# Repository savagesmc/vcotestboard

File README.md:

# MAX2607 (Voltage Controlled Oscillator) Test Board.

this is an open source schemaatic and board layout for the [MAX2607 VCO](https://www.analog.com/en/products/max2607.html).

Analog Devices is selling their eval boards for over $200 USD, and the part itself is
just a couple of bucks. I'm just getting started desiging my own hardware,
so I figured I might as well practice my board design skills. I simply copied
The [eval board design taken from the Analog Devices website](
https://www.analog.com/media/en/technical-documentation/data-sheets/MAX2605EVKIT-MAX2609EVKIT.pdf).
I included placeholders for all of the resistors and inductors called out in that design,
so this board should work for testing all versions of the chip from the MAX2605
to the MAX2609.

I ordered 5 of these from [JLCPCB](https://jlcpcb.com). It was a very simple
process. I simply took the contents of the [gerbers folder](./gerbers), zipped
them up and uploaded the zipfile, and for $40 USD (including shipping), and about
2 weeks, I have a set of boards.

The version of the boards I ordered was commit 27e65ae6c2ac64e3f9bb4, which I later
noticed had a few things missing from the silkscreen, and I forgot to do the
mounting holes. I fixed those things, and that is the main HEAD commit.

So for about $12 USD total per board (board and parts), I now have 5 of these test boards.

If these devices pan out, I may use them in some future designs I am thinking through.

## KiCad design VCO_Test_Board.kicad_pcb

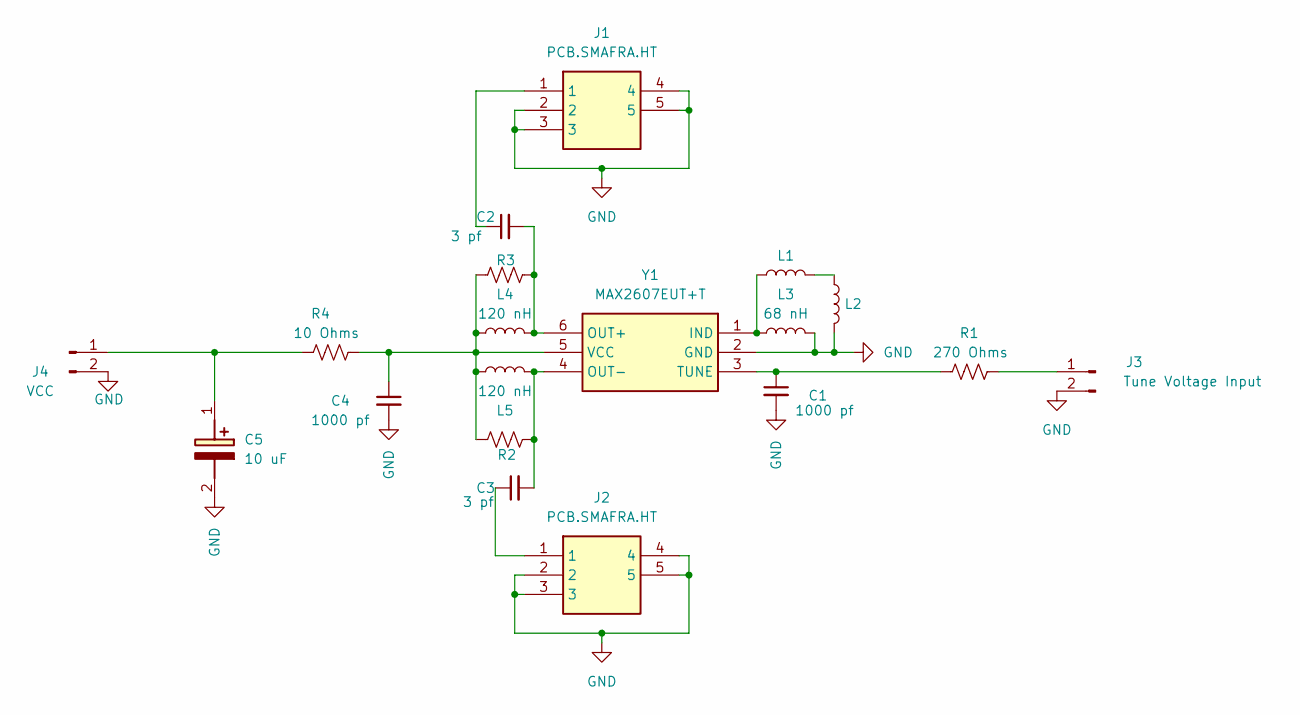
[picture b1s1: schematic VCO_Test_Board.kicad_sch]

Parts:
C1, C4: 1000 pf; C_1206_3216Metric
C2, C3: 3 pf; C_1206_3216Metric
C5: 10 uF; CAPPM6032X280N; Mouser Part Number 581-TAJC106K016
J1, J2: PCB.SMAFRA.HT; PCBSMAFRAHT; Mouser Part Number 960-PCB.SMAFRA.HT
J3: Tune Voltage Input; PinHeader_1x02_P2.54mm_Vertical
J4: VCC; PinHeader_1x02_P2.54mm_Vertical
L1, L2: L_0805_2012Metric
L3: 68 nH; L_0805_2012Metric
L4, L5: 120 nH; L_0805_2012Metric
R1: 270 Ohms; R_0805_2012Metric_Pad1.20x1.40mm_HandSolder
R2, R3: R_0805_2012Metric_Pad1.20x1.40mm_HandSolder
R4: 10 Ohms; R_0805_2012Metric_Pad1.20x1.40mm_HandSolder
Y1: MAX2607EUT+T; SOT95P280X145-6N; Mouser Part Number 700-MAX2607EUTT

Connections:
GND: C1.2, C4.2, C5.2 (-), J1.2, J1.3, J1.4, J1.5, J2.2, J2.3, J2.4, J2.5, J3.2, J4.2, L2.2, L3.2, Y1.2 (GND)
unnamed: C2.1, J1.1
unnamed: C3.1, J2.1
unnamed: C5.1 (+), J4.1, R4.1
unnamed: J3.1, R1.2
unnamed: L1.2, L2.1
unnamed: L1.1, L3.1, Y1.1 (IND)
unnamed: C2.2, L4.2, R3.2, Y1.6 (OUT+)
unnamed: C3.2, L5.2, R2.2, Y1.4 (OUT-)
unnamed: C1.1, R1.1, Y1.3 (TUNE)
unnamed: C4.1, L4.1, L5.1, R2.1, R3.1, R4.2, Y1.5 (VCC)

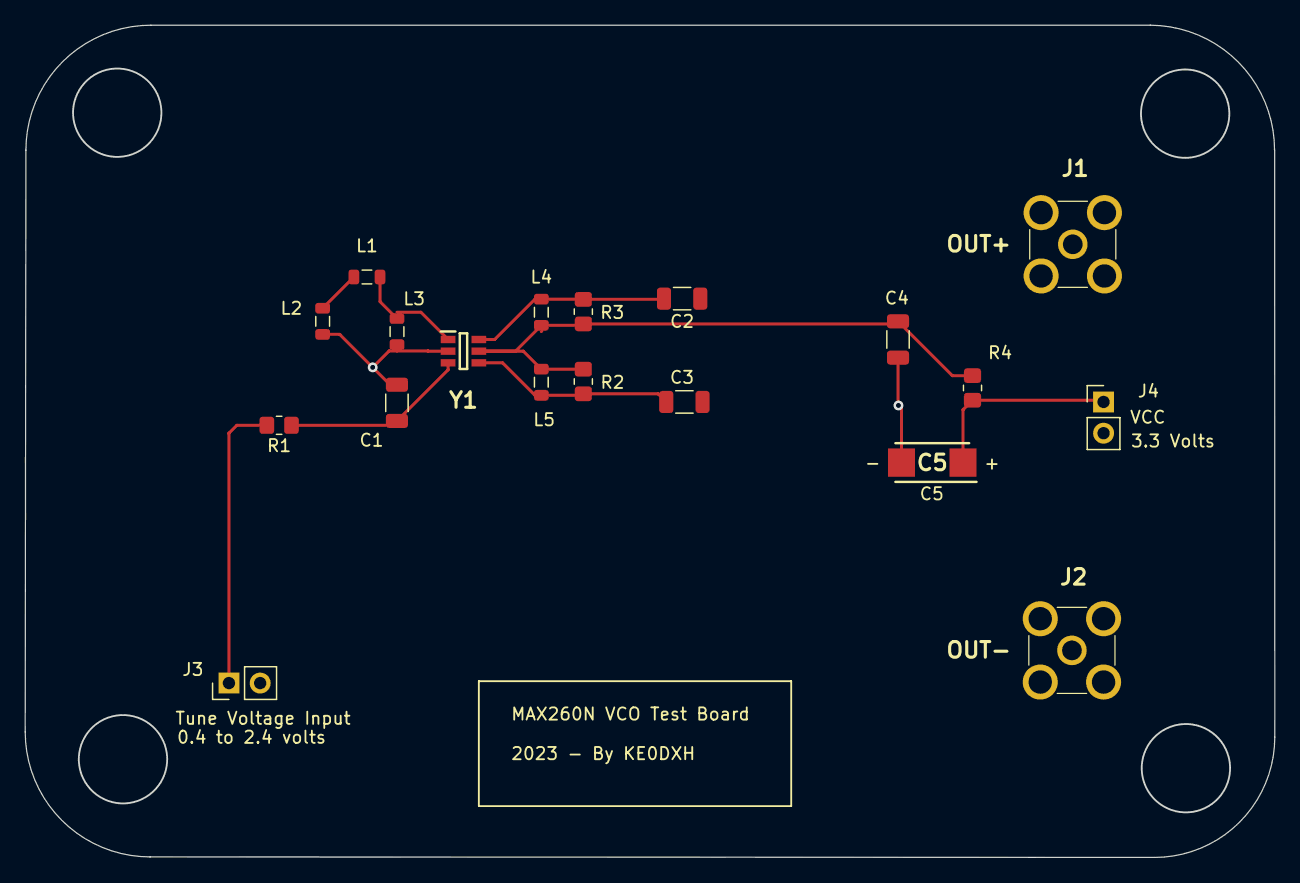
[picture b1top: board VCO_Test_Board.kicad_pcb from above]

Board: 2 copper layers, 101.6 x 67.6 mm, 19 parts (0 on the bottom side), 11 nets.

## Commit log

2023-10-09 Add initial board design/layout.
2023-10-10 Export gerber files.
2023-10-10 Swap out C5 for Tantalum capacitor. Final export for board order.
2023-10-10 Add mounting holes. Fix silkscreen in a few places.
2023-10-10 Update README with a little info
2023-10-10 Fix README.
